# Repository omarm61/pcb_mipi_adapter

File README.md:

# mipi_adapter
Hardware design for a MIPI to USB adapter

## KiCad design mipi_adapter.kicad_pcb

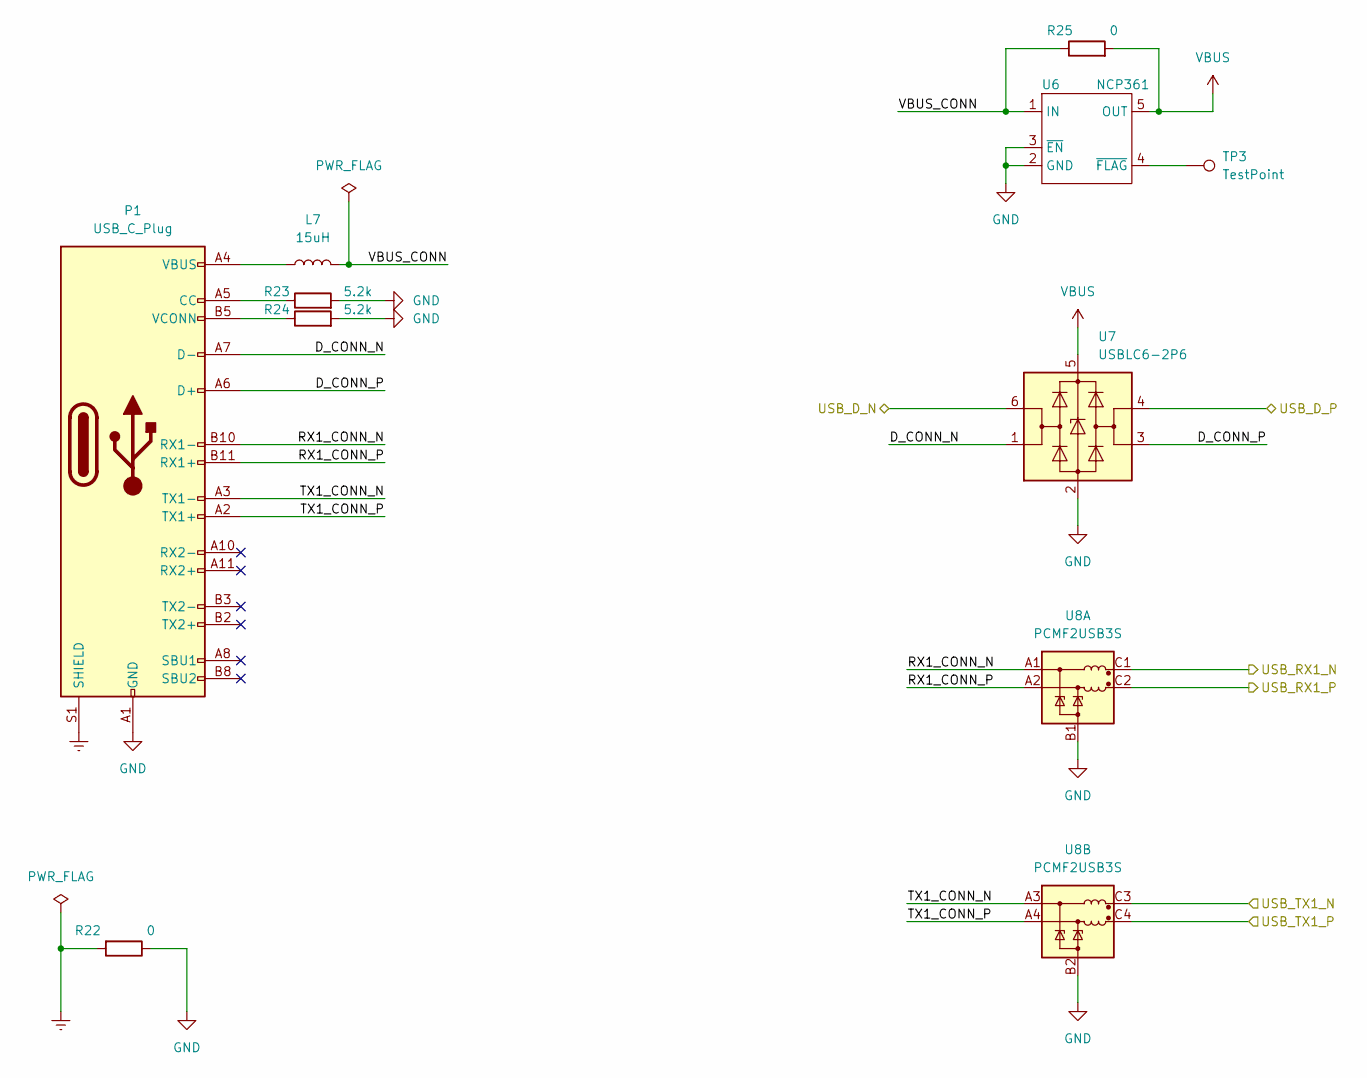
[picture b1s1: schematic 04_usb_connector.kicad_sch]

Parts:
L7: 15uH; L_0603_1608Metric
P1: USB_C_Plug; USB_C_Receptacle_GCT_USB4105-xx-A_16P_TopMnt_Horizontal
R22, R25: 0; R_0603_1608Metric
R23, R24: 5.2k; R_0603_1608Metric
TP3: TestPoint; TestPoint_THTPad_D1.0mm_Drill0.5mm
U6: NCP361; udfn-6_2x2
U7: USBLC6-2P6; SOT-666
U8: PCMF2USB3S; Nexperia_WLCSP-10_4-2-4_1.57x1.17mm_Layout6x3_P0.4mm

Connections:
/CPU/USB_D_N: U7.6 (I/O1); also elsewhere on the board
/CPU/USB_D_P: U7.4 (I/O2); also elsewhere on the board
/CPU/USB_RX1_N: U8.C1 (CH2_OUT+); also elsewhere on the board
/CPU/USB_RX1_P: U8.C2 (CH2_OUT-); also elsewhere on the board
/CPU/USB_TX1_N: U8.C3 (CH2_OUT+); also elsewhere on the board
/CPU/USB_TX1_P: U8.C4 (CH2_OUT-); also elsewhere on the board
/USB Connector/D_CONN_N: P1.A7 (D-), U7.1 (I/O1)
/USB Connector/D_CONN_P: P1.A6 (D+), U7.3 (I/O2)
/USB Connector/RX1_CONN_N: P1.B10 (RX1-), U8.A1 (CH2_IN+)
/USB Connector/RX1_CONN_P: P1.B11 (RX1+), U8.A2 (CH2_IN-)
/USB Connector/TX1_CONN_N: P1.A3 (TX1-), U8.A3 (CH2_IN+)
/USB Connector/TX1_CONN_P: P1.A2 (TX1+), U8.A4 (CH2_IN-)
/USB Connector/VBUS_CONN: L7.2, R25.1, U6.1 (IN)
Earth: P1.S1 (SHIELD), R22.2
GND: P1.A1 (GND), P1.A12 (GND), P1.B1 (GND), P1.B12 (GND), R22.1, R23.2, R24.2, U6.2 (GND), U6.3 (~EN), U7.2 (GND), U8.B1 (GND_CH2), U8.B2 (GND_CH2); also elsewhere on the board
unnamed: L7.1, P1.A4 (VBUS), P1.A9 (VBUS), P1.B4 (VBUS), P1.B9 (VBUS)
unnamed: P1.A5 (CC), R23.1
unnamed: P1.B5 (VCONN), R24.1
unnamed: TP3.1, U6.4 (~FLAG)
VBUS: R25.2, U6.5 (OUT), U7.5 (VBUS); also elsewhere on the board

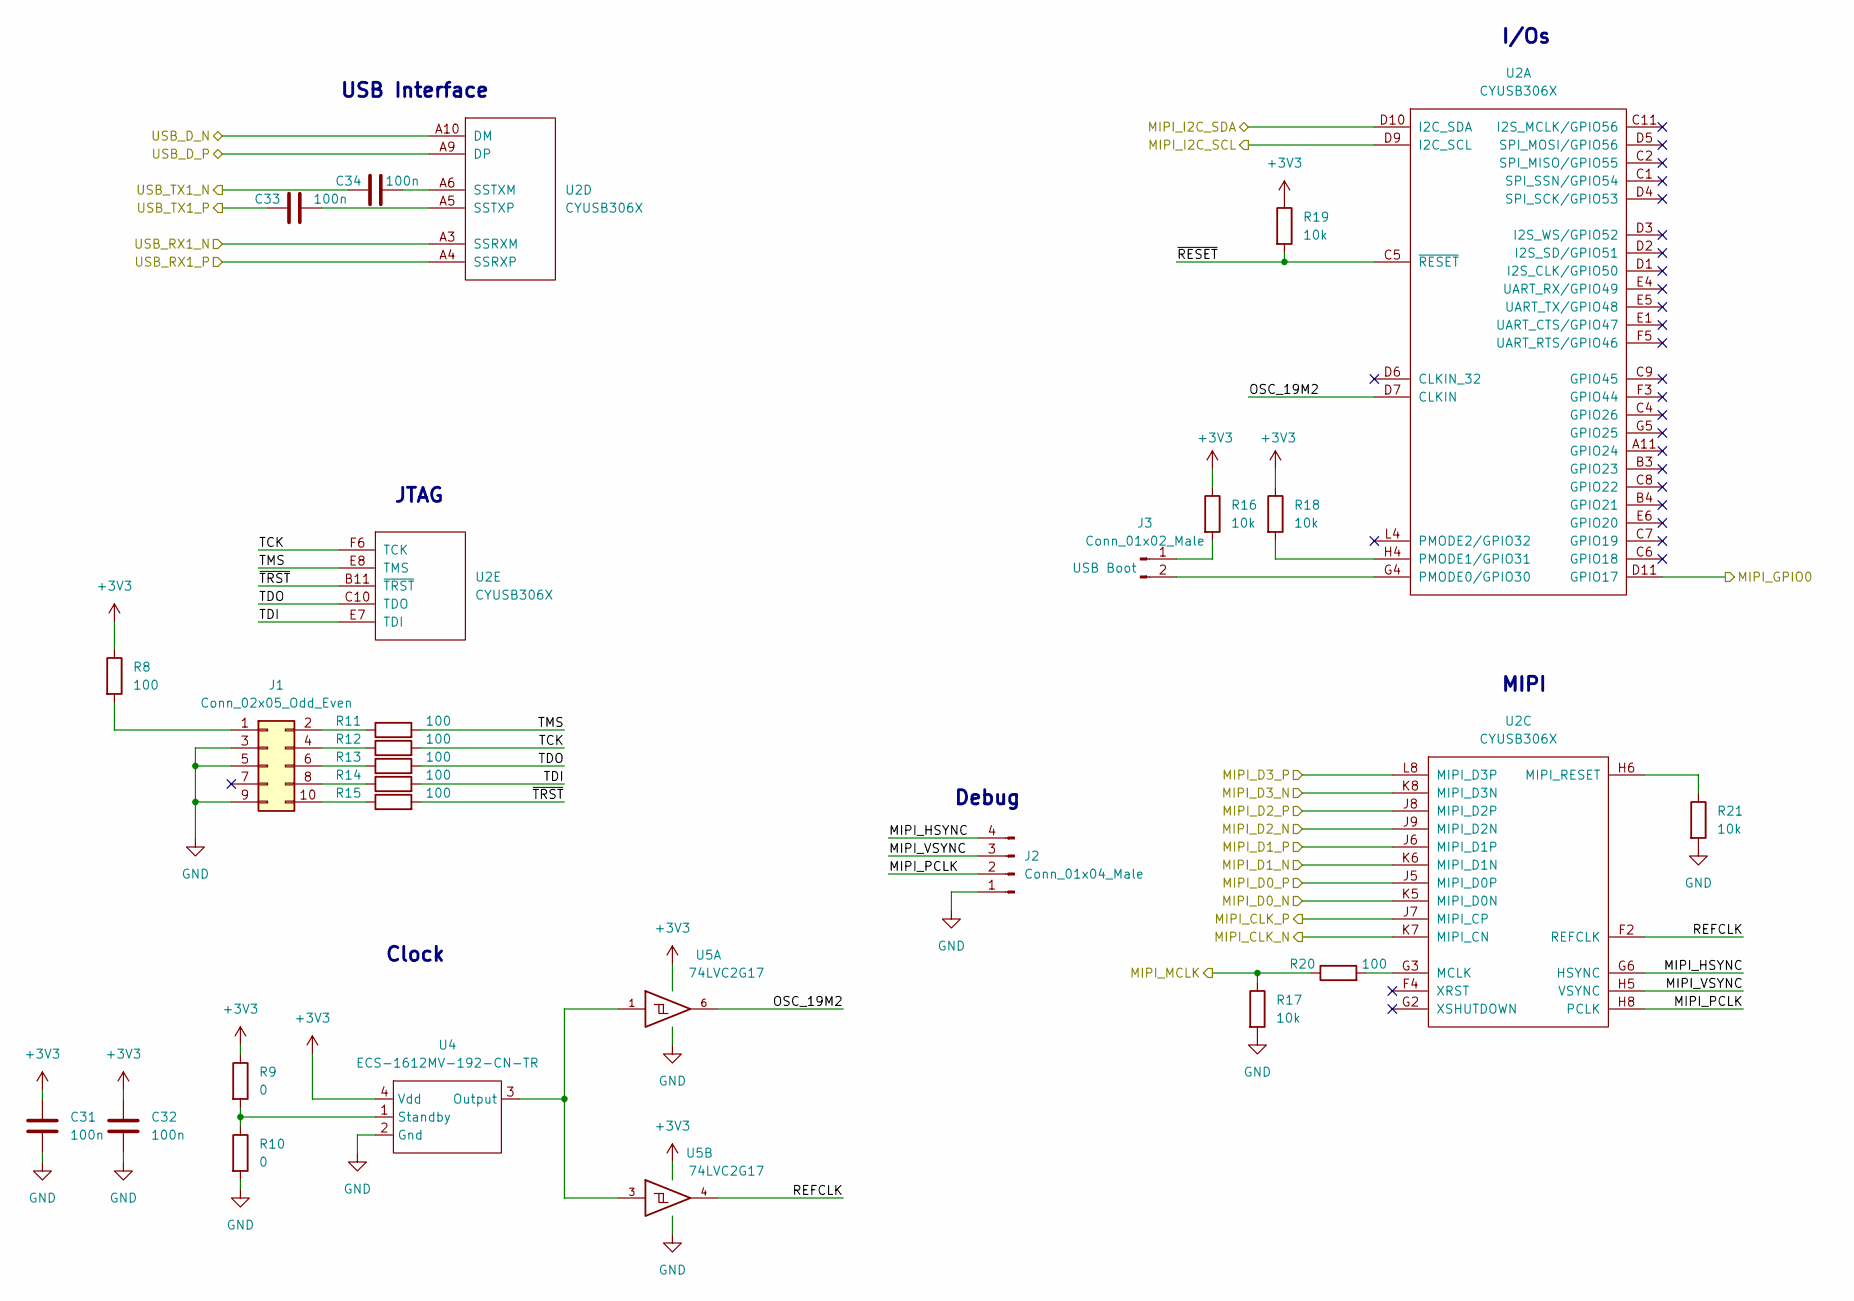
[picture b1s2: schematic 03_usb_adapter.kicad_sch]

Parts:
C31, C32, C33, C34: 100n; C_0603_1608Metric
J1: Conn_02x05_Odd_Even; PinHeader_2x05_P2.00mm_Vertical
J2: Conn_01x04_Male; PinHeader_1x04_P2.00mm_Vertical
J3: Conn_01x02_Male; PinSocket_1x02_P2.00mm_Vertical
R8, R11, R12, R13, R14, R15, R20: 100; R_0603_1608Metric
R9, R10: 0; R_0603_1608Metric
R16, R17, R18, R19, R21: 10k; R_0603_1608Metric
U2: CYUSB306X; XBGA-121_10x10mm_Layout11x11_P0.8mm
U4: ECS-1612MV-192-CN-TR; Crystal_SMD_ECS_1.6x1.2
U5: 74LVC2G17; SOT-363_SC-70-6

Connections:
+3V3: C31.1, C32.1, R8.1, R9.1, R16.1, R18.1, R19.1, U4.4 (Vdd), U5.5 (VCC); also elsewhere on the board
/CPU/MIPI_CLK_N: U2.K7 (MIPI_CN); also elsewhere on the board
/CPU/MIPI_CLK_P: U2.J7 (MIPI_CP); also elsewhere on the board
/CPU/MIPI_D0_N: U2.K5 (MIPI_D0N); also elsewhere on the board
/CPU/MIPI_D0_P: U2.J5 (MIPI_D0P); also elsewhere on the board
/CPU/MIPI_D1_N: U2.K6 (MIPI_D1N); also elsewhere on the board
/CPU/MIPI_D1_P: U2.J6 (MIPI_D1P); also elsewhere on the board
/CPU/MIPI_D2_N: U2.J9 (MIPI_D2N); also elsewhere on the board
/CPU/MIPI_D2_P: U2.J8 (MIPI_D2P); also elsewhere on the board
/CPU/MIPI_D3_N: U2.K8 (MIPI_D3N); also elsewhere on the board
/CPU/MIPI_D3_P: U2.L8 (MIPI_D3P); also elsewhere on the board
/CPU/MIPI_GPIO0: U2.D11 (GPIO17); also elsewhere on the board
/CPU/MIPI_HSYNC: J2.4, U2.G6 (HSYNC)
/CPU/MIPI_MCLK: R17.1, R20.1; also elsewhere on the board
/CPU/MIPI_PCLK: J2.2, U2.H8 (PCLK)
/CPU/MIPI_VSYNC: J2.3, U2.H5 (VSYNC)
/CPU/OSC_19M2: U2.D7 (CLKIN), U5.6
/CPU/REFCLK: U2.F2 (REFCLK), U5.4
/CPU/TCK: R12.2, U2.F6 (TCK)
/CPU/TDI: R14.2, U2.E7 (TDI)
/CPU/TDO: R13.2, U2.C10 (TDO)
/CPU/TMS: R11.2, U2.E8 (TMS)
/CPU/USB_D_N: U2.A10 (DM); also elsewhere on the board
/CPU/USB_D_P: U2.A9 (DP); also elsewhere on the board
/CPU/USB_RX1_N: U2.A3 (SSRXM); also elsewhere on the board
/CPU/USB_RX1_P: U2.A4 (SSRXP); also elsewhere on the board
/CPU/USB_TX1_N: C34.1; also elsewhere on the board
/CPU/USB_TX1_P: C33.1; also elsewhere on the board
/CPU/~RESET: R19.2, U2.C5 (~RESET)
/CPU/~TRST: R15.2, U2.B11 (~TRST)
/MIPI Connector/I2C_SCL: U2.D9 (I2C_SCL); also elsewhere on the board
/MIPI Connector/I2C_SDA: U2.D10 (I2C_SDA); also elsewhere on the board
GND: C31.2, C32.2, J1.3, J1.5, J1.9, J2.1, R10.2, R17.2, R21.2, U4.2 (Gnd), U5.2 (GND); also elsewhere on the board
unnamed: C33.2, U2.A5 (SSTXP)
unnamed: C34.2, U2.A6 (SSTXM)
unnamed: J1.1, R8.2
unnamed: J1.2, R11.1
unnamed: J1.4, R12.1
unnamed: J1.6, R13.1
unnamed: J1.8, R14.1
unnamed: J1.10, R15.1
unnamed: J3.1, R16.2
unnamed: J3.2, U2.G4 (PMODE0/GPIO30)
unnamed: R9.2, R10.1, U4.1 (Standby)
unnamed: R18.2, U2.H4 (PMODE1/GPIO31)
unnamed: R20.2, U2.G3 (MCLK)
unnamed: R21.1, U2.H6 (MIPI_RESET)
unnamed: U4.3 (Output), U5.1, U5.3

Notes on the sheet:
Debug
I/Os
JTAG
Clock
MIPI
USB Interface

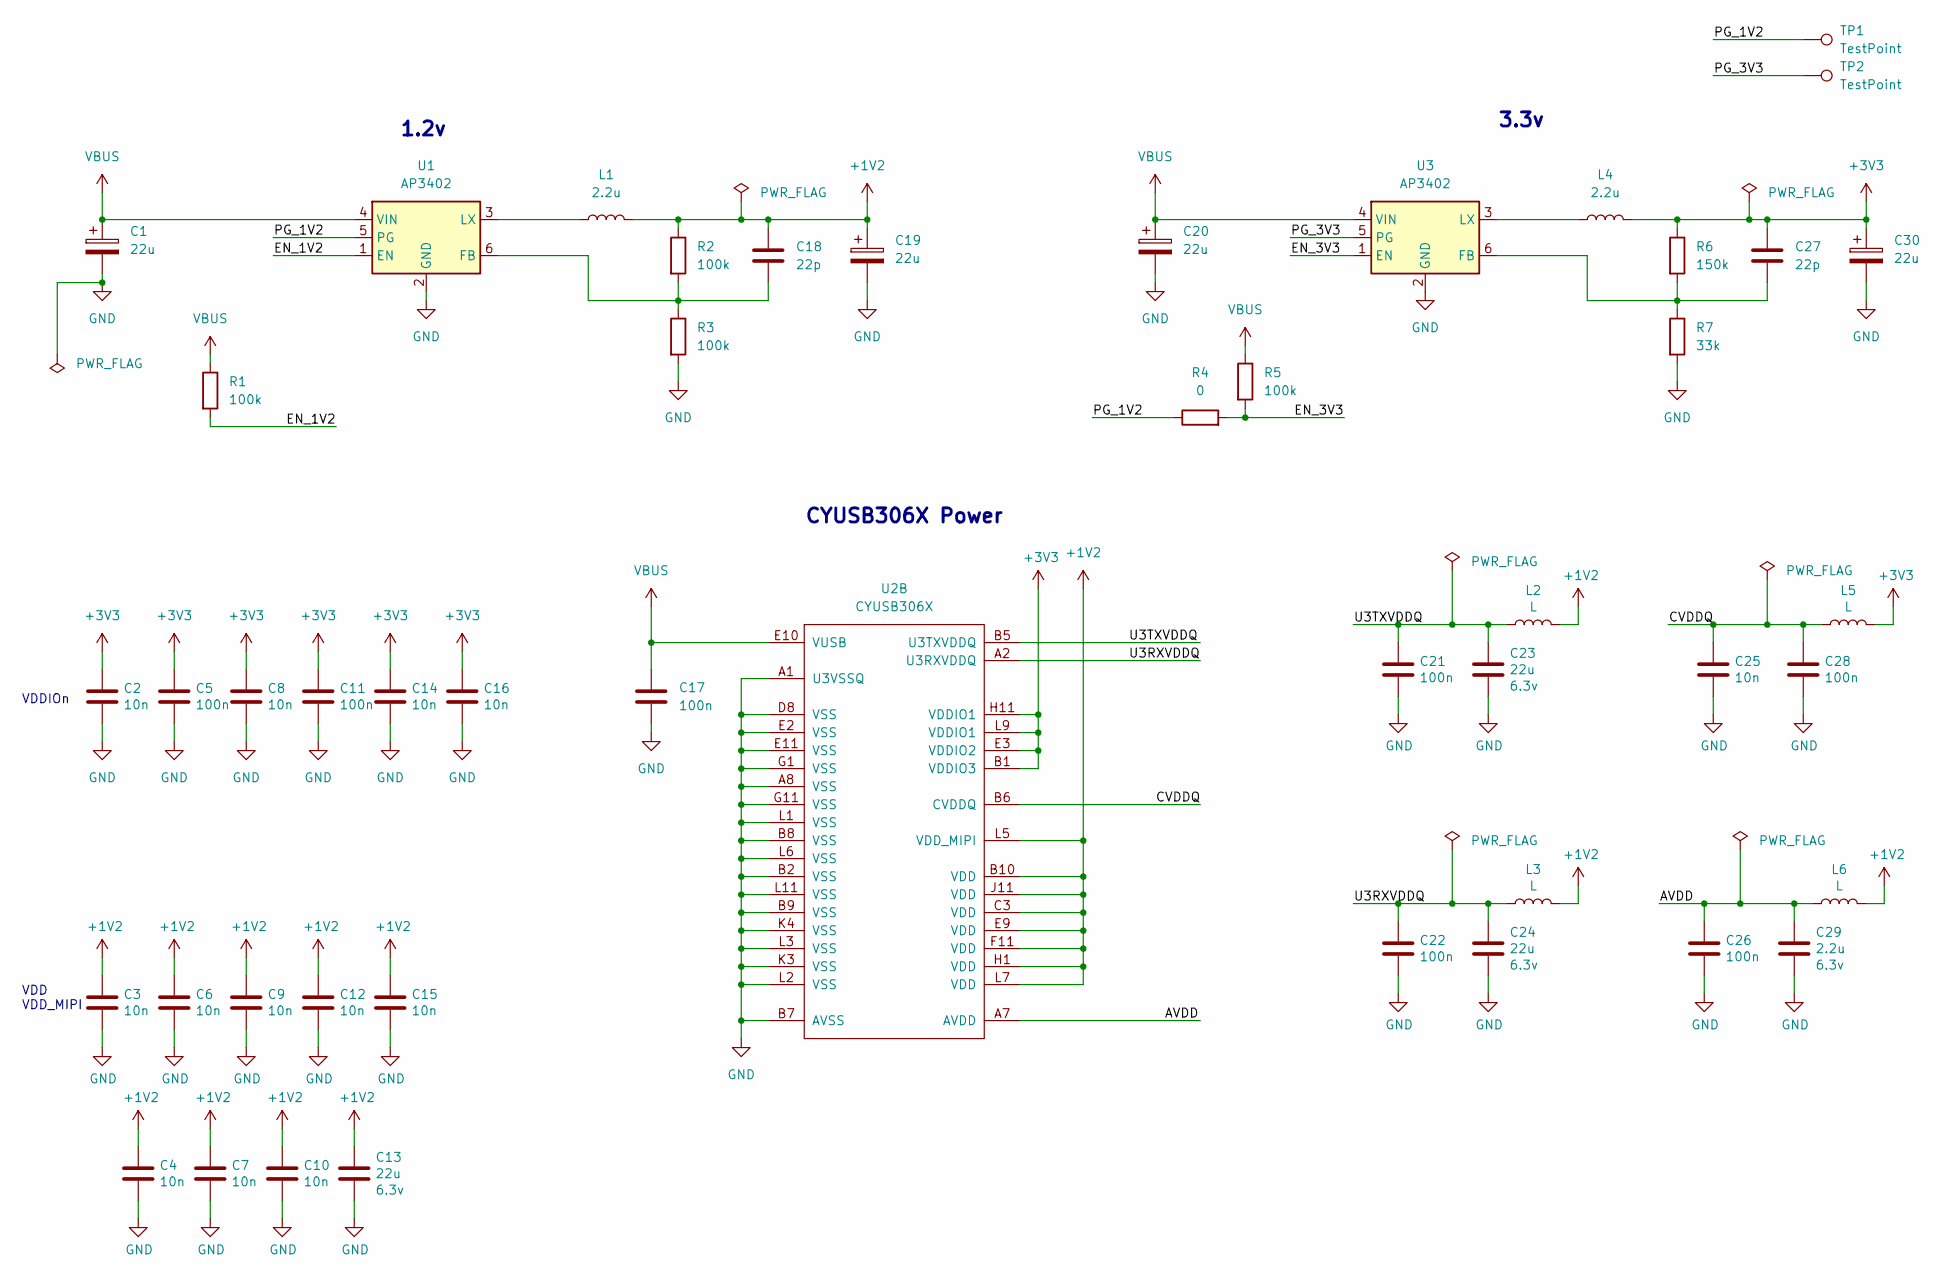
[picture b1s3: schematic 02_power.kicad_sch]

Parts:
C1, C19, C20, C30: 22u; CP_EIA-3216-18_Kemet-A
C2, C3, C4, C6, C7, C8, C9, C10, C12, C14, C15, C16: 10n; C_0402_1005Metric
C5, C11: 100n; C_0402_1005Metric
C13: 22u; C_0402_1005Metric; rating 6.3v
C17, C21, C22, C26, C28: 100n; C_0603_1608Metric
C18, C27: 22p; C_0603_1608Metric
C23, C24: 22u; C_0603_1608Metric; rating 6.3v
C25: 10n; C_0603_1608Metric
C29: 2.2u; C_0603_1608Metric; rating 6.3v
L1, L4: 2.2u; L_Neosid_SMS-ME3015
L2, L3, L5, L6: L; L_0603_1608Metric
R1, R2, R3, R5: 100k; R_0603_1608Metric
R4: 0; R_0603_1608Metric
R6: 150k; R_0603_1608Metric
R7: 33k; R_0603_1608Metric
TP1, TP2: TestPoint; TestPoint_THTPad_D1.0mm_Drill0.5mm
U1, U3: AP3402; TSOT-23-6
U2: CYUSB306X; XBGA-121_10x10mm_Layout11x11_P0.8mm

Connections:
+1V2: C3.1, C4.1, C6.1, C7.1, C9.1, C10.1, C12.1, C13.1, C15.1, C18.1, C19.1, L1.2, L2.2, L3.2, L6.2, R2.1, U2.B10 (VDD), U2.C3 (VDD), U2.E9 (VDD), U2.F11 (VDD), U2.H1 (VDD), U2.J11 (VDD), U2.L5 (VDD_MIPI), U2.L7 (VDD)
+3V3: C2.1, C5.1, C8.1, C11.1, C14.1, C16.1, C27.1, C30.1, L4.2, L5.2, R6.1, U2.B1 (VDDIO3), U2.E3 (VDDIO2), U2.H11 (VDDIO1), U2.L9 (VDDIO1); also elsewhere on the board
/Power/AVDD: C26.1, C29.1, L6.1, U2.A7 (AVDD)
/Power/CVDDQ: C25.1, C28.1, L5.1, U2.B6 (CVDDQ)
/Power/EN_1V2: R1.2, U1.1 (EN)
/Power/EN_3V3: R4.2, R5.2, U3.1 (EN)
/Power/PG_1V2: R4.1, TP1.1, U1.5 (PG)
/Power/PG_3V3: TP2.1, U3.5 (PG)
/Power/U3RXVDDQ: C22.1, C24.1, L3.1, U2.A2 (U3RXVDDQ)
/Power/U3TXVDDQ: C21.1, C23.1, L2.1, U2.B5 (U3TXVDDQ)
GND: C1.2, C2.2, C3.2, C4.2, C5.2, C6.2, C7.2, C8.2, C9.2, C10.2, C11.2, C12.2, C13.2, C14.2, C15.2, C16.2, C17.2, C19.2, C20.2, C21.2, C22.2, C23.2, C24.2, C25.2, C26.2, C28.2, C29.2, C30.2, R3.2, R7.2, U1.2 (GND), U2.A1 (U3VSSQ), U2.A8 (VSS), U2.B2 (VSS), U2.B7 (AVSS), U2.B8 (VSS), U2.B9 (VSS), U2.D8 (VSS), U2.E2 (VSS), U2.E11 (VSS), U2.G1 (VSS), U2.G11 (VSS), U2.K3 (VSS), U2.K4 (VSS), U2.L1 (VSS), U2.L2 (VSS), U2.L3 (VSS), U2.L6 (VSS), U2.L11 (VSS), U3.2 (GND); also elsewhere on the board
unnamed: C18.2, R2.2, R3.1, U1.6 (FB)
unnamed: C27.2, R6.2, R7.1, U3.6 (FB)
unnamed: L1.1, U1.3 (LX)
unnamed: L4.1, U3.3 (LX)
VBUS: C1.1, C17.1, C20.1, R1.1, R5.1, U1.4 (VIN), U2.E10 (VUSB), U3.4 (VIN); also elsewhere on the board

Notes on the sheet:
VDD VDD_MIPI
VDDIOn
1.2v
CYUSB306X Power
3.3v

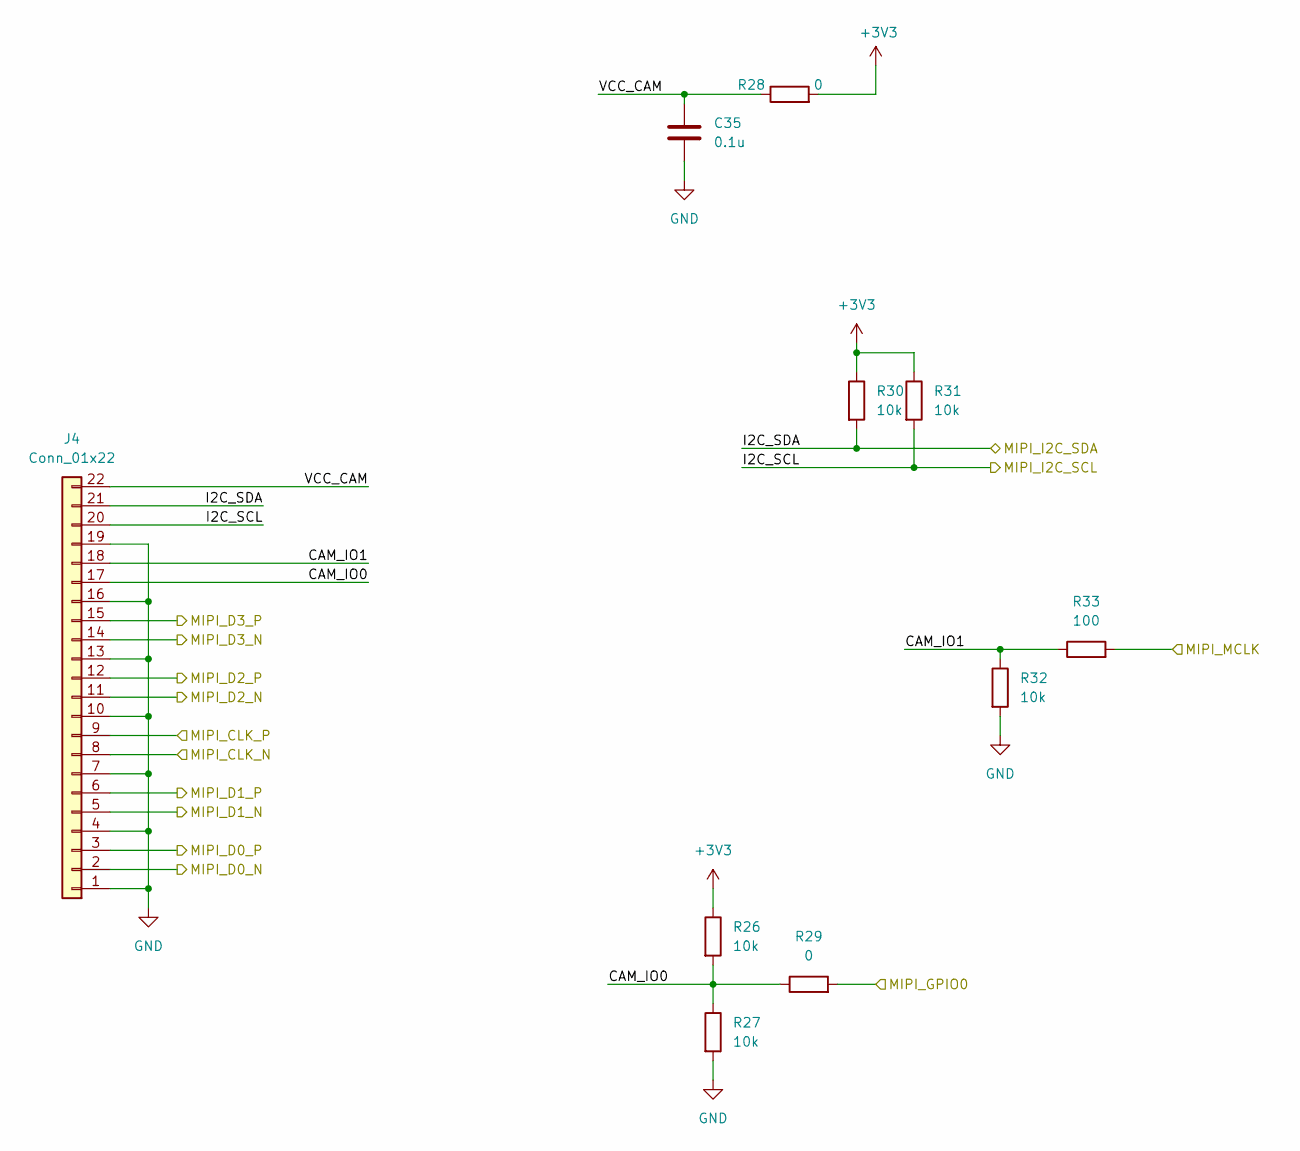
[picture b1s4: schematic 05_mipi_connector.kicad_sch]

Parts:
C35: 0.1u; C_0603_1608Metric
J4: Conn_01x22; Hirose_FH12-22S-0.5SH_1x22-1MP_P0.50mm_Horizontal
R26, R27, R30, R31, R32: 10k; R_0603_1608Metric
R28, R29: 0; R_0603_1608Metric
R33: 100; R_0603_1608Metric

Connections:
+3V3: R26.1, R28.2, R30.1, R31.1; also elsewhere on the board
/CPU/MIPI_CLK_N: J4.8; also elsewhere on the board
/CPU/MIPI_CLK_P: J4.9; also elsewhere on the board
/CPU/MIPI_D0_N: J4.2; also elsewhere on the board
/CPU/MIPI_D0_P: J4.3; also elsewhere on the board
/CPU/MIPI_D1_N: J4.5; also elsewhere on the board
/CPU/MIPI_D1_P: J4.6; also elsewhere on the board
/CPU/MIPI_D2_N: J4.11; also elsewhere on the board
/CPU/MIPI_D2_P: J4.12; also elsewhere on the board
/CPU/MIPI_D3_N: J4.14; also elsewhere on the board
/CPU/MIPI_D3_P: J4.15; also elsewhere on the board
/CPU/MIPI_GPIO0: R29.2; also elsewhere on the board
/CPU/MIPI_MCLK: R33.2; also elsewhere on the board
/MIPI Connector/CAM_IO0: J4.17, R26.2, R27.1, R29.1
/MIPI Connector/CAM_IO1: J4.18, R32.1, R33.1
/MIPI Connector/I2C_SCL: J4.20, R31.2; also elsewhere on the board
/MIPI Connector/I2C_SDA: J4.21, R30.2; also elsewhere on the board
/MIPI Connector/VCC_CAM: C35.1, J4.22, R28.1
GND: C35.2, J4.1, J4.4, J4.7, J4.10, J4.13, J4.16, J4.19, R27.2, R32.2; also elsewhere on the board

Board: 2 copper layers, 91 parts (0 on the bottom side), 73 nets, no tracks yet.

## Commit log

2023-08-28 First push
2023-08-28 added usb-c connector
2023-09-05 finished usb interface and added some new components
2023-09-05 adde symbols and footprints
2023-09-07 added mipi connector
2023-09-14 finished first pass of the schematics
2023-09-15 cleaned up some DRC errors
2023-09-27 finished schematics
